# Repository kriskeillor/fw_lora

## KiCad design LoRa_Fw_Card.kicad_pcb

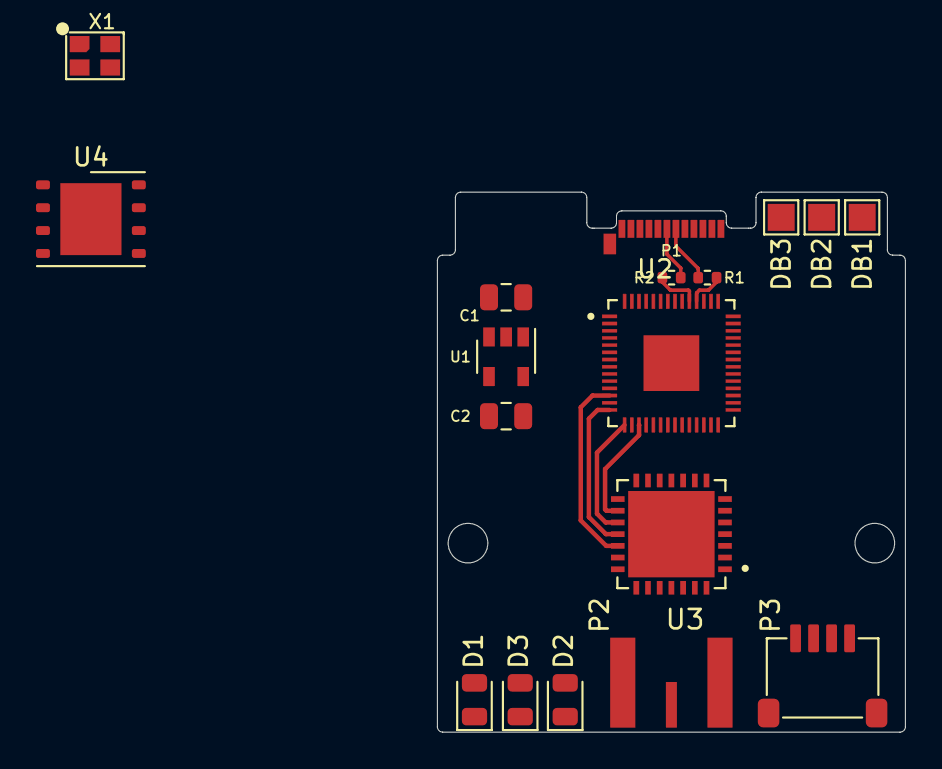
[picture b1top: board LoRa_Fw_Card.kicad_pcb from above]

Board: 2 copper layers, 26.0 x 30.0 mm, 20 parts (0 on the bottom side), 28 nets.

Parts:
C1, C2: 10uF; C_0805_2012Metric
D1, D2, D3: LED; LED_0805_2012Metric
DB1, DB2, DB3: TestPoint; TestPoint_Pad_1.5x1.5mm
H1, H2: MountingHole; MountingHole_2.2mm_M2
P1: USB_C_Plug_USB2.0; USB_C_Plug_Molex_105444
P2: 60312202114513; SMA_Female_Edge_60312202114513
P3: Conn_01x04_Male; CCSH-W10R-04
R1, R2: R_Small; R_0402_1005Metric
U1: AP2112K-3.3; SOT-23-5
U2: RP2040TR7; QFN40P700X700X90-57N
U3: SX1276IMLTRT; QFN65P600X600X100-29N
U4: W25Q128JVS; WSON-8-1EP_6x5mm_P1.27mm_EP3.4x4mm
X1: WE-SPXO Crystal Osc 12.00MHz; Oscillator_SMD_4pin_2.5x2.0mm

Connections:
+1V1: U2.23 (DVDD), U2.45 (VREG_VOUT), U2.50 (DVDD)
+3V3: C2.1, U1.5 (VOUT), U2.1 (IOVDD), U2.10 (IOVDD), U2.22 (IOVDD), U2.33 (IOVDD), U2.42 (IOVDD), U2.43 (ADC_AVDD), U2.44 (VREG_VIN), U2.48 (USB_VDD), U2.49 (IOVDD), U4.8 (VCC)
/MCU Core/MEM_CLK: U2.52 (QSPI_SCLK), U4.6 (CLK)
/MCU Core/MEM_CS_N: U2.56 (QSPI_SS_N), U4.1 (~CS)
/MCU Core/MEM_D0: U2.53 (QSPI_SD0), U4.5 (DI(IO0))
/MCU Core/MEM_D1: U2.55 (QSPI_SD1), U4.2 (DO(IO1))
/MCU Core/MEM_D2: U2.54 (QSPI_SD2), U4.3 (IO2)
/MCU Core/MEM_D3: U2.51 (QSPI_SD3), U4.7 (IO3)
/MCU Core/RF_CS_N: U2.12 (GPIO9), U3.19 (NSS)
/MCU Core/RF_DIO0: U2.28 (GPIO17), U3.8 (DIO0)
/MCU Core/RF_DIO1: U2.29 (GPIO18), U3.9 (DIO1/DCLK)
/MCU Core/RF_DIO2: U2.30 (GPIO19), U3.10 (DIO2/DATA)
/MCU Core/RF_DIO3: U2.31 (GPIO20), U3.11 (DIO3)
/MCU Core/RF_DIO4: U2.32 (GPIO21), U3.12 (DIO4)
/MCU Core/RF_DIO5: U2.34 (GPIO22), U3.13 (DIO5)
/MCU Core/RF_MISO: U2.15 (GPIO12), U3.17 (MISO)
/MCU Core/RF_MOSI: U2.14 (GPIO11), U3.18 (MOSI)
/MCU Core/RF_RST_N: U2.35 (GPIO23), U3.7 (NRESET)
/MCU Core/RF_SCLK: U2.17 (GPIO14), U3.16 (SCK)
/MCU Core/USB_DN: R1.2, U2.46 (USB_DM)
/MCU Core/USB_DP: R2.2, U2.47 (USB_DP)
/MCU Core/XOSC: U2.20 (XIN), X1.3 (OUT)
/Power/D+: P1.A6 (D+), R2.1
/Power/D-: P1.A7 (D-), R1.1
GND: C1.2, C2.2, P1.A1 (GND), P1.A12 (GND), P1.B1 (GND), P1.B12 (GND), P1.S1 (SHIELD), U1.2 (GND), U2.19 (TESTEN), U3.15 (GND), U3.23 (GND), U3.26 (GND), U3.29 (GND), U4.4 (GND), X1.2 (GND)
unnamed: P2.2, P2.3, P2.4, P2.5
unnamed: X1.1 (Stby), X1.4 (Vs)
VBUS: C1.1, P1.A4 (VBUS), P1.A9 (VBUS), P1.B4 (VBUS), P1.B9 (VBUS), U1.1 (VIN), U1.3 (EN)

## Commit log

2022-12-20 Add partial RF and Memory wiring and placement

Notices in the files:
LoRa_Fw_Card.kicad_pcb:
This work is licensed under a Creative Commons Attribution 4.0 International License
